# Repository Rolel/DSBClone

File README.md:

# DSB Clone
This is a replacement board for the SEGA Digital Sound Boards 1 and 2 used on several SEGA arcade games.

# Historical background

The SEGA Digital Sound Boards 1 and 2 are dedicated to playing music (the BGMs) on several SEGA games. The music is stored in maskroms specific to each game. It is a card separate from the main stack of the game, sometimes located in its own cage.

They bear the following references: *837-10084 DIGITAL AUDIO BD SEGA 1993, 171-6614B PC BD, Sticker: 837-12941* and *837-12273 DIGITAL SOUND BD 2 SEGA 1995, 171-7165D PC BD, Sticker: 837-12273-92, Sticker: 837-13376*. These original cards are not very reliable and become difficult to find at a reasonable price.

They were used on the following games:

* First version (DSB1):
  * Daytona USA
  * Desert Tank
  * Manx TT Deluxe
  * Scud Race / Super GT (Model 3 Step 1.5)
  * Sega Rally Deluxe
  * Sega Touring Cars (Model 2C CRX)
  * Star Wars Arcade (Model 1)
  * Virtua Cop
  * Virtua Fighter
  * Virtua Racing
  * Wing Wars

*Please note that Daytona USA, Virtua Racing, Virtua Fighter, Wing War & Star Wars Arcade use DSB1 with an addon board in charge of playing sounds. The DSBclone doesn't handle this. As a result I suggest you avoid clone for such games and **DSB1 support is disabled by default in source code**.*

* Second version (DSB2):
  * Daytona 2
  * Lost World
  * Sega Rally 2
  * Spikeout
  * Spikeout FE
  * Star Wars Trilogy
  * Top Skater

# Features

* Playback of MP3 and WAV files stored on a microSD card
* Plug'n'Play: no modification of the wiring
* Track listing can be modified simply by renumbering the files
* Output volume identical to the original DSB
* Reprogrammable firmware: based on an Arduino Nano
* 24-bit DAC, DR 90dB, SNR 85 dB
* Protection by fuse and polarizers on the connectors
* 2 audio outputs with "JST SEGA" connector

In comparison with the original card:
* There is a slight latency (a few milliseconds) when starting the music. This can be understood if you pay attention with a twin that contains a DSB Sega and a DSB Clone. We can play on the MP3 to reset everything, or simply put two clones.
* The sound quality is much better: high quality MP3 / WAV replace the original 112kbits MPEG2.
* Possibility to customize the game's BGMs.

# Build 

## PCB

You can build the PCB with PCBway services. Upload the `DSBclone.kicad_pcb.zip` file to the "Quick order" tool and keep the default settings. That's all !

It can be even easier: use the shared project: https://www.pcbway.com/project/shareproject/DSB_Clone_replacement_for_SEGA_Digital_Sound_Boards_1_and_2_b2268928.html 

## BOM:
* U1: HCPL-0600 SOIC-8 optocoupler
* D1, D4: any diode that can handle 1A (T7 is ok)
* D2: 0805 led
* D3: 0805 1N4148, used to drop down DfPlayer voltage
* R1,R3,R5: 0805 1k resistor
* R2,R4: 0805 470o resistor
* F1: 0805 1A fuse
* DfPlayer: get the original one from reliable source (Mouser, Farnell...) and not an AliExpress clone.
* Arduino Nano: a 328p is ok.
* CN5: IDC 2x5 vertical connector
* CN6,7: JST B5P SH
* CN1: JST B6P SH 
* SPK, DBG, MidiRX: debug header, shouldn't be populated unless you want to develop

# Updating from release

Update procedure can be found in [Docs/Update.md](Docs/Update.md).

# Releases

Public releases can be found in the [Releases](Releases/) folder. Update procedure can be found in [Docs/Update.md](Docs/Update.md) documentation.

The "-debug.hex" releases have debugging enabled. You can hook a RS232 adapter to the debug pin on the board (default 115200bps, 8 data bits, 0 parity bit).

Public releases:

* 2021-08-29: 
  * Fix a bug on fadeout. 
  * Improvements on latency by filtering spam sent by games to the player.
* 2022-04-02: 
  * Change fadeout behavior; sound volume is now restored after fade.
  * Latency of MP3 player is tested on start; this improves latency.
* 2022-04-03:
  * Fix intro sound not being played on some MP3 players.
  * Fix advertisement BGM on Scud Race.
* 2022-04-05:
  * Fix a case where sound effects would affect BGM.
* 2022-04-06:
  * Reverted advertisement BGM played by DSB on Scud Race.
  * Track looping now working on Scud Race.
* 2022-04-16:
  * Track loop bugfix for Scud Race.
* 2022-12-04:
  * Removed support of DSB1 command set as they conflict with some DSB2 games.
* 2024-01-04:
  * Improvements on calibration for clone/original MP3 module. Releases available for DSB2, DSB1 & SpikeOut.
* 2024-08-24:
  * A special source code is proposed for SpikeOut FE. It compress sound volume to be closer to the original game.

# Installation

1. Prepare the SD card.

Any microSD card will do: between 60 and 150MB of space is sufficient. If you have an old 128 or 256MB card that's fine.

The audio files are to be placed in the "MP3" directory located at the root. Each file is preceded by 4 digits corresponding to the track number.
Bonus: the "1000_xxx.mp3" file is automatically read when the card is started. A cool way to have a jingle, music on hold, etc. Personally I put the "SEGAAAA" jingle 

Several packs corresponding to the most common games are available. Here are those currently known:
* Sega Rally 2, CD quality from OST: https://segaretro.org/Sega_Rally_2_(album)
* Scud Race, CD quality from OST: https://segaretro.org/Scud_Race_Sound_Tracks
* Daytona2, CD quality from OST: https://segaretro.org/Daytona_USA_2_Sound_Tracks
* VirtuaRacing, dump arcade from Khinsider VGM
* In progress: Virtua Fighter, CD quality from OST: https://segaretro.org/Virtua_Fighter_&_Virtua_Fighter_2_Music_Tracks
* Numbers: all numbers from 1 to 100. This allows you to know which track is requested by the game without needing a computer.

As they are copyrighted materials they are not shared.

2. Connect to the arcade cabinet

It's plug'n'play without modifying the wiring:
* the black 10 pin socket for the power supply
* the 6-pin white socket for MIDI
* the white 5-pin socket(s) for the audio outputs

# Ready to use board

You can buy a ready to use board on arcade forums like [Neo-Arcadia](https://www.neo-arcadia.com/forum/viewtopic.php?f=9&t=75510) (French) or [Arcade Projects](https://www.arcade-projects.com/threads/dsb-clone-digital-sound-board-sega.17832/) (English).

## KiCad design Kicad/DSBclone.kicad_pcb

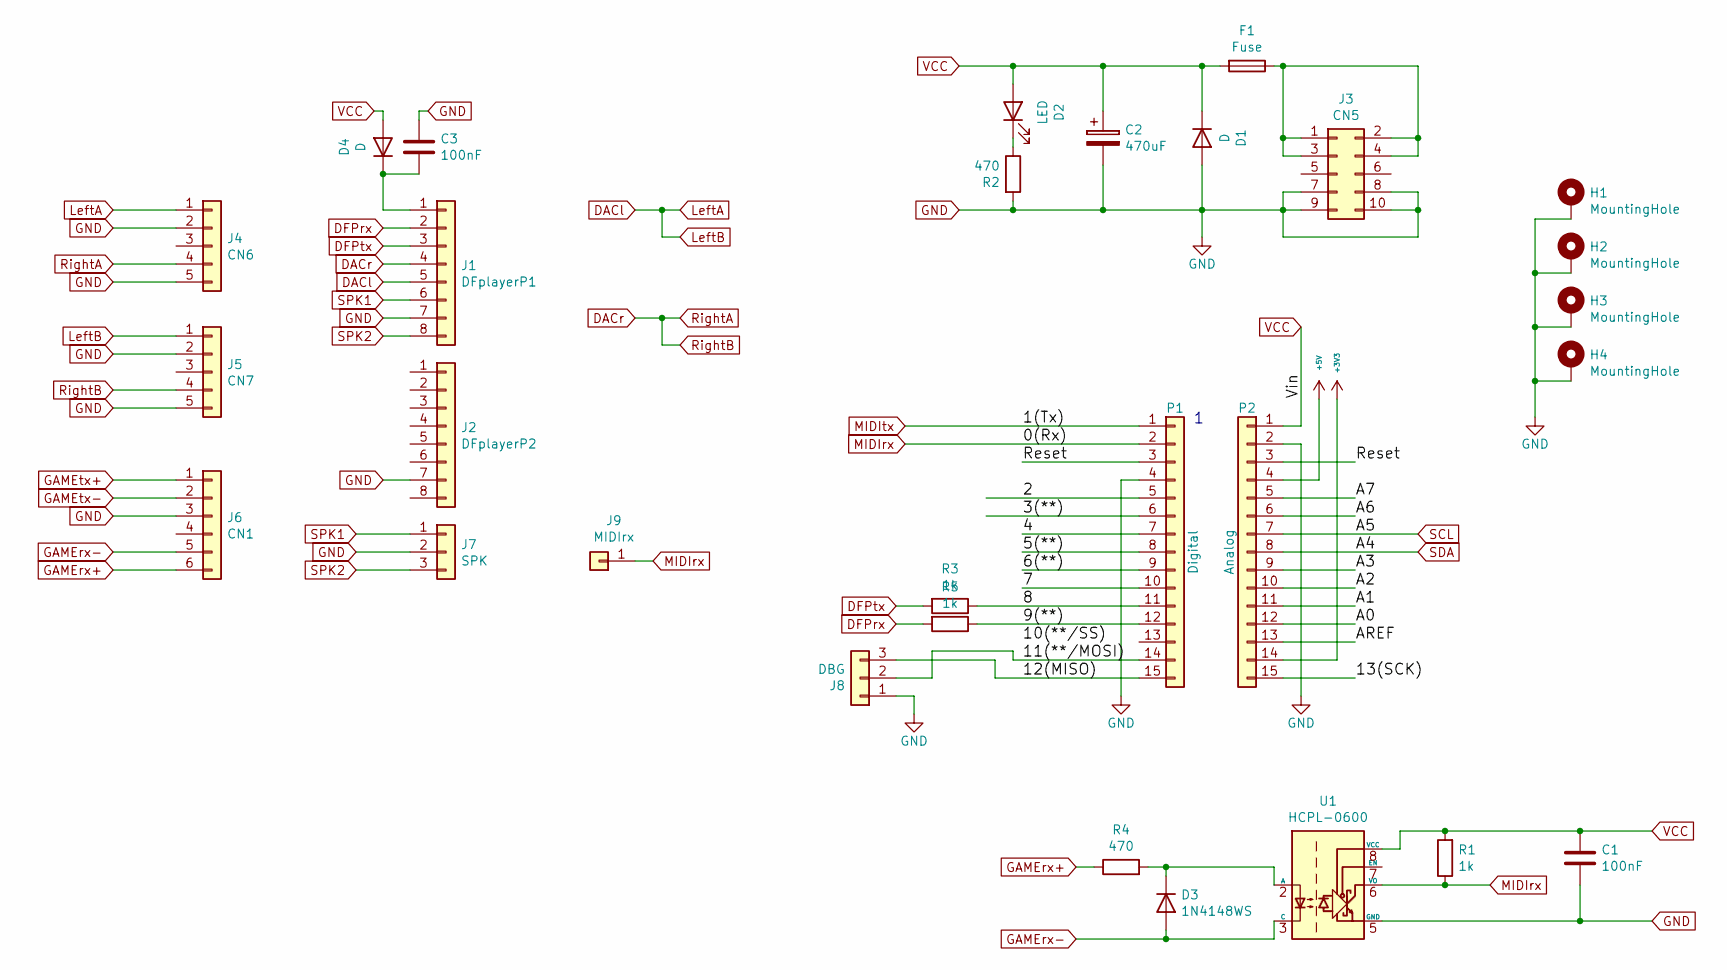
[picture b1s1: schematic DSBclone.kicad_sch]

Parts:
C1, C3: 100nF; C_0805_2012Metric_Pad1.18x1.45mm_HandSolder
C2: 470uF; CP_Radial_D5.0mm_P2.50mm
D1, D4: D; D_0805_2012Metric_Pad1.15x1.40mm_HandSolder
D2: LED; LED_0805_2012Metric_Pad1.15x1.40mm_HandSolder
D3: 1N4148WS; D_SOD-323_HandSoldering
F1: Fuse; Fuse_0805_2012Metric_Pad1.15x1.40mm_HandSolder
H1, H2, H3, H4: MountingHole; MountingHole_3.2mm_M3_DIN965_Pad
J1: DFplayerP1; PinSocket_1x08_P2.54mm_Vertical
J2: DFplayerP2; PinSocket_1x08_P2.54mm_Vertical
J3: CN5; IDC-Header_2x05_P2.54mm_Vertical
J4: CN6; PinHeader_1x05_P2.54mm_Vertical
J5: CN7; PinHeader_1x05_P2.54mm_Vertical
J6: CN1; PinHeader_1x06_P2.54mm_Vertical
J7: SPK; PinHeader_1x03_P2.54mm_Vertical
J8: DBG; PinHeader_1x03_P2.54mm_Vertical
J9: MIDIrx; PinHeader_1x01_P2.54mm_Vertical
P1: Digital; PinSocket_1x15_P2.54mm_Vertical
P2: Analog; PinSocket_1x15_P2.54mm_Vertical
R1, R3, R5: 1k; R_0805_2012Metric_Pad1.20x1.40mm_HandSolder
R2, R4: 470; R_0805_2012Metric_Pad1.20x1.40mm_HandSolder
U1: HCPL-0600; SOIC-8_3.9x4.9mm_P1.27mm

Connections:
+3V3: P2.14
+5V: P2.4
/2: P1.5
/3(**): P1.6
/4: P1.7
/5(**): P1.8
/6(**): P1.9
/7: P1.10
/8: P1.11, R3.1
/9(**): P1.12, R5.1
/11(**/MOSI): J8.2, P1.14
/12(MISO): J8.3, P1.15
/13(SCK): P2.15
/A0: P2.12
/A1: P2.11
/A2: P2.10
/A3: P2.9
/A6: P2.6
/A7: P2.5
/AREF: P2.13
/Reset: P1.3, P2.3
DACl: J1.5, J4.1, J5.1
DACr: J1.4, J4.4, J5.4
DFPrx: J1.2, R5.2
DFPtx: J1.3, R3.2
GAMErx+: J6.6, R4.1
GAMErx-: D3.2 (A), J6.5, U1.3 (C)
GAMEtx+: J6.1
GAMEtx-: J6.2
GND: C1.2, C2.2, C3.1, D1.2 (A), H1.1, H2.1, H3.1, H4.1, J1.7, J2.7, J3.7, J3.8, J3.9, J3.10, J4.2, J4.5, J5.2, J5.5, J6.3, J7.2, J8.1, P1.4, P2.2, R2.2, U1.5 (GND)
MIDIrx: J9.1, P1.2, R1.1, U1.6 (VO)
MIDItx: P1.1
unnamed: D2.1 (K), R2.1
unnamed: D3.1 (K), R4.2, U1.2 (A)
unnamed: C3.2, D4.1 (K), J1.1
unnamed: F1.1, J3.1, J3.2, J3.3, J3.4
SCL: P2.7
SDA: P2.8
SPK1: J1.6, J7.1
SPK2: J1.8, J7.3
VCC: C1.1, C2.1, D1.1 (K), D2.2 (A), D4.2 (A), F1.2, P2.1, R1.2, U1.8 (VCC)

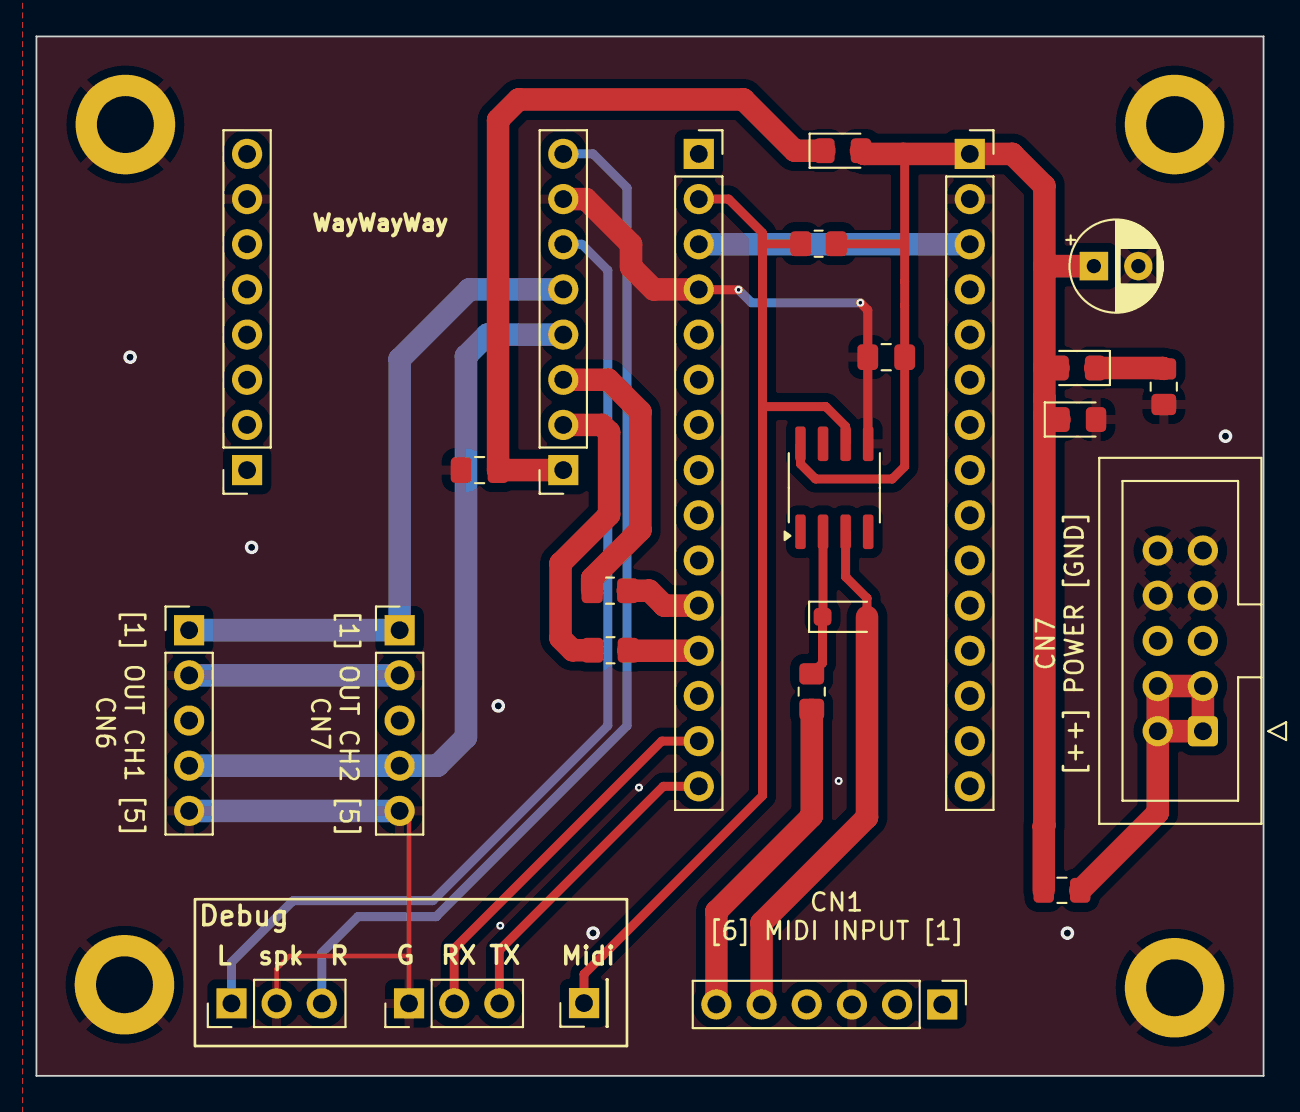
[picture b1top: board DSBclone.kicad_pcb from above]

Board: 2 copper layers, 69.0 x 58.4 mm, 29 parts (0 on the bottom side), 20 nets.

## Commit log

2021-08-29 Readme init
2021-08-29 Release 2021-08-29; improve fadeout and responsiveness
2021-08-29 Pictures and update documentation
2021-08-29 Add pictures to Readme
2021-08-29 Init update procedure
2021-08-29 Xloader screenshots
2021-08-29 Add pictures
2021-08-29 XLoader software
2021-08-29 Link to update procedure and arcade forums
2021-08-29 Releases link and infos
2021-08-29 Fix release description
2022-04-02 New release! Improve fadeout compatibility. Improve latency.
2022-04-02 Fix release
2022-04-02 Fadeout now restores previous sound volume. Fix SCUD Race support
2022-04-03 Fix intro sound and Advertisement BGM on Scud Race.
2022-04-04 Fix a case where sound effects would affect BGM
2022-04-05 Reverted advert BGM being played by DSB on Scud Race.
2022-04-06 Track loop is now working on Scud Race.
2022-04-06 Fix changelog
2022-04-16 Fix for repeated tracks
2022-12-04 Fix the Spikeout test mode. Remove DSB1 command set support.
2022-12-04 Publish source code and build instructions.
2023-07-31 Update README.md
    Add Daytona USA to the list of DSB1 games with optional sound board
2024-01-04 Remove a wrong debug message
2024-01-04 Added a patch for Spikeout. Added NL to calibration error message.
2024-01-04 Optimized division - replaced by bitshift
2024-01-04 Better calibration for borh original and clone MP3 modules
2024-01-04 Added NL to calibration error message.
2024-01-04 Clean release.
2024-01-04 Clean release for DSB2, DSB1 and Spikeout.
2024-08-24 Special build for SpikeOut FE. Sound volume is compressed to be closer to original game.
2024-10-13 Updated hardware section in Readme. Updated the PCB to remove digipot and simplify build. Uploaded the Kicad 8.0 files.
2024-10-14 Add PCBway project link.
